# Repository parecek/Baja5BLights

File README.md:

# Baja5BLights
Lights and IR transponder for rc car Baja 5B. Front, rear lights including brake. Schematic, pcb (Kicad), Arduino sw

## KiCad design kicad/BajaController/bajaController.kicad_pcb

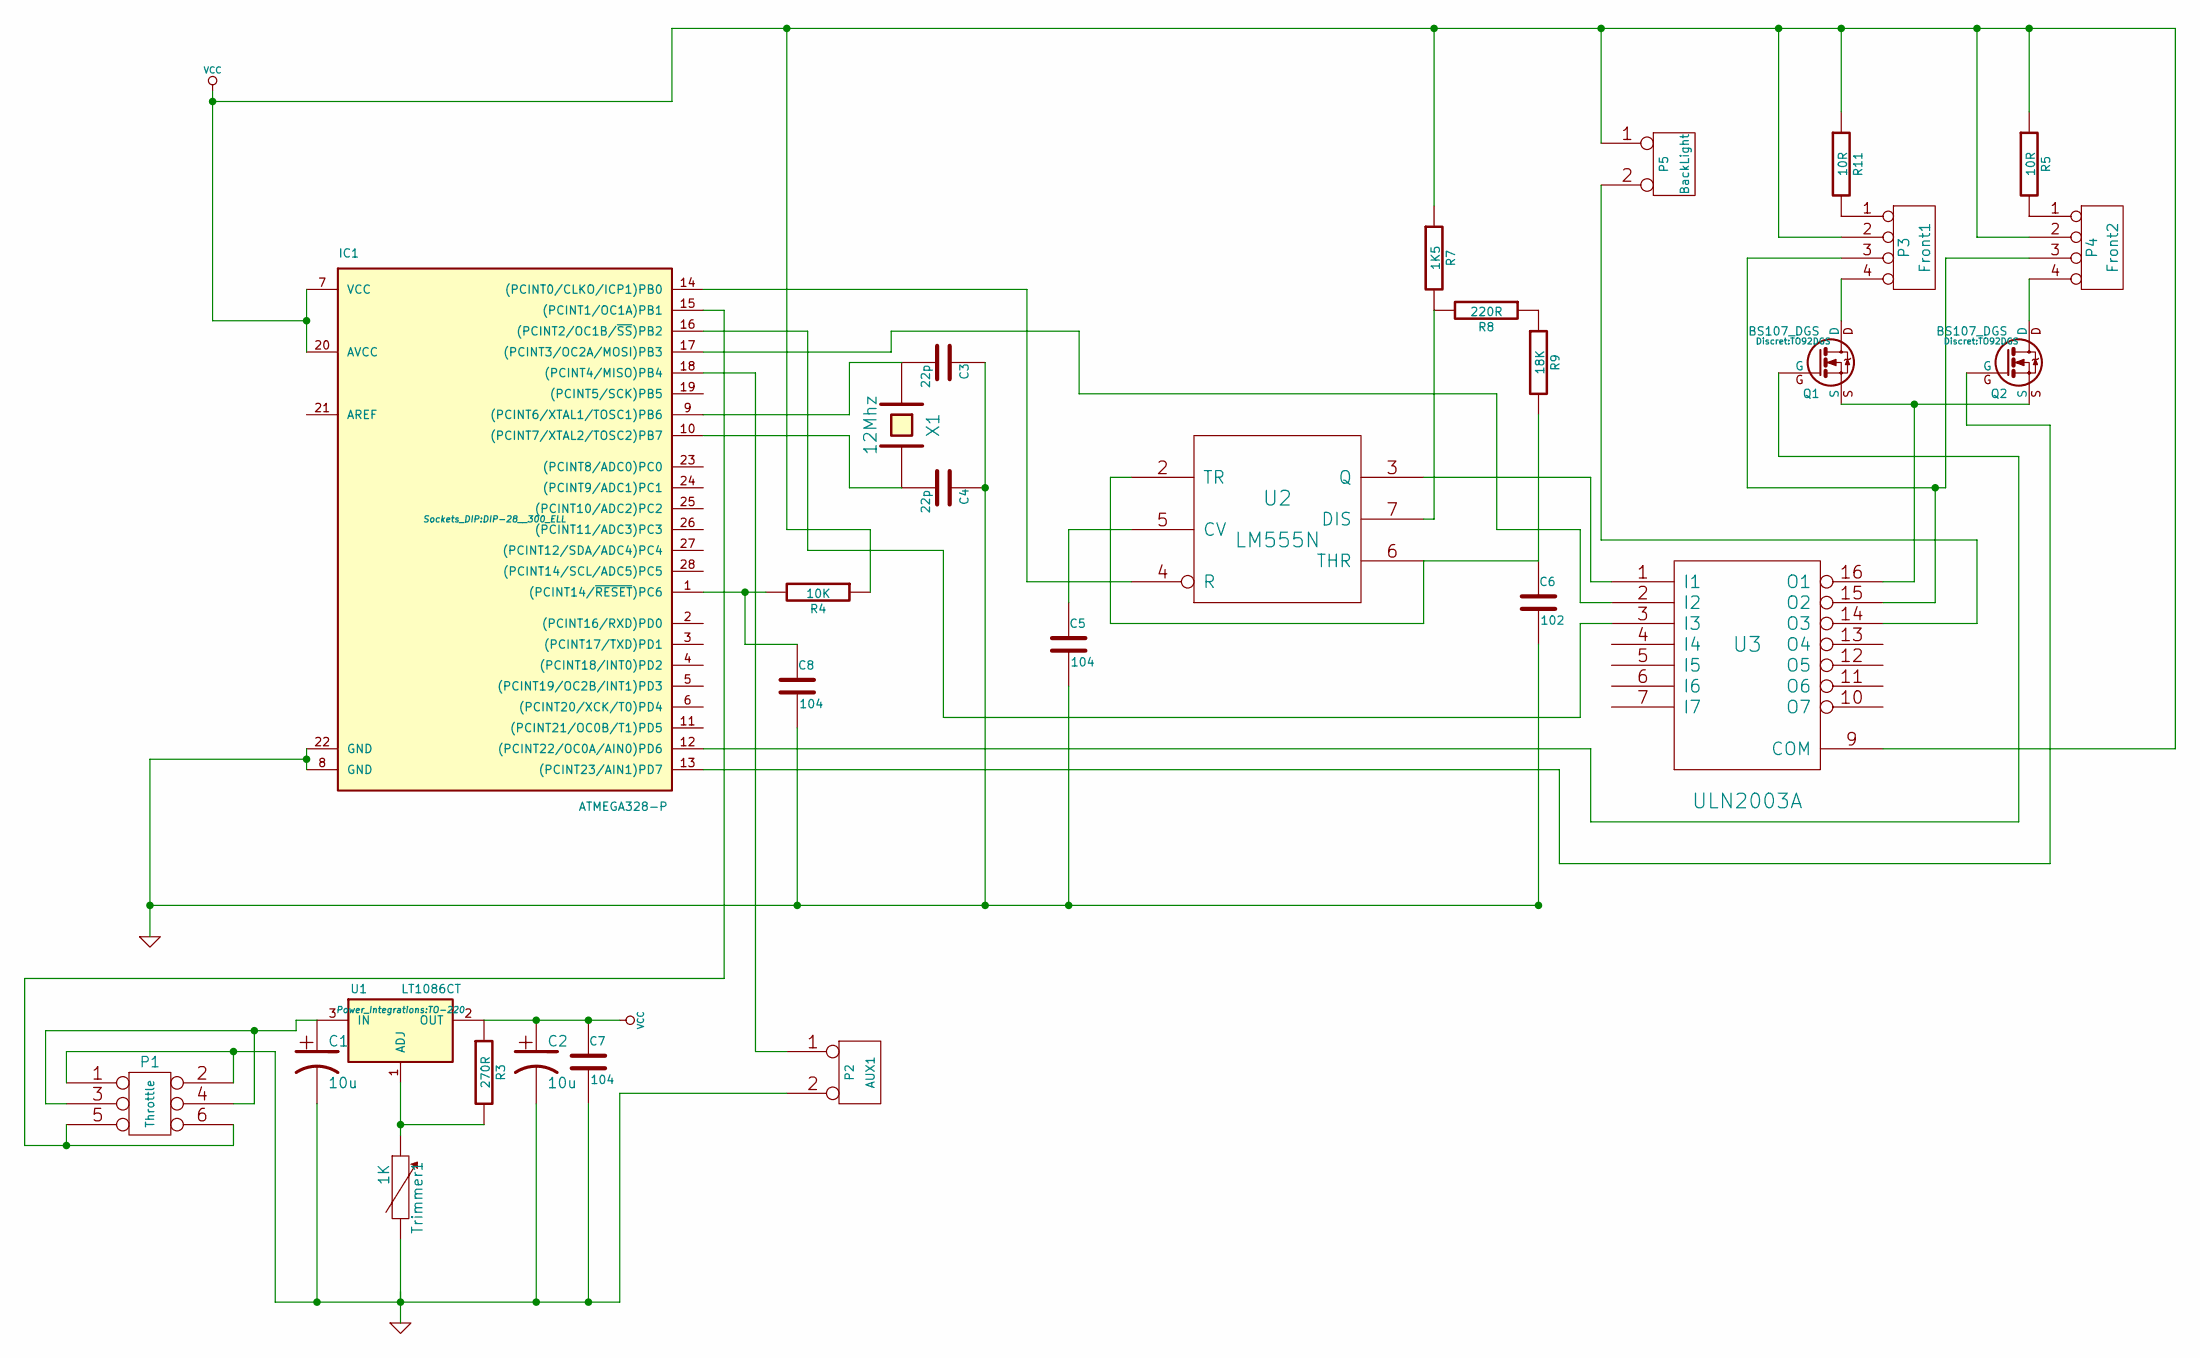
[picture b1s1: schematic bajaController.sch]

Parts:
C1, C2: 10u; C1V5
C3, C4: 22p; C_1206_HandSoldering
C5, C7, C8: 104; C2
C6: 102; C2
IC1: ATMEGA328-P; DIP-28__300_ELL
P1: Throttle; Pin_Header_Straight_2x03
P2: AUX1; Pin_Header_Straight_1x02
P3: Front1; Pin_Header_Straight_1x04
P4: Front2; Pin_Header_Straight_1x04
P5: BackLight; Pin_Header_Straight_1x02
Q1, Q2: BS107_DGS; TO92DGS
R3: 270R; R_1206_HandSoldering
R4: 10K; R_1206_HandSoldering
R5, R11: 10R; R_1206_HandSoldering
R7: 1K5; R_1206_HandSoldering
R8: 220R; R_1206_HandSoldering
R9: 18K; R_1206_HandSoldering
Trimmer1: 1K; Trimmer_CA6V5
U1: LT1086CT; TO-220
U2: LM555N; DIP-8__300_ELL
U3: ULN2003A; DIP-16__300_ELL
X1: 12Mhz; Crystal_HC49-U_Vertical

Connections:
GND: C1.2, C2.2, C3.1, C4.1, C5.2, C6.2, C7.2, C8.2, IC1.8 (GND), IC1.22 (GND), P1.1, P1.2, P2.2 (PM), Trimmer1.2, U2.1 (GND), U3.8 (GND)
unnamed: C1.1, P1.3, P1.4, U1.3 (IN)
unnamed: C3.2, IC1.9 ((PCINT6/XTAL1/TOSC1)PB6), X1.1
unnamed: C4.2, IC1.10 ((PCINT7/XTAL2/TOSC2)PB7), X1.2
unnamed: C5.1, U2.5 (CV)
unnamed: C6.1, R9.2, U2.2 (TR), U2.6 (THR)
unnamed: C8.1, IC1.1 ((PCINT14/~RESET~)PC6), R4.2
unnamed: IC1.12 ((PCINT22/OC0A/AIN0)PD6), Q1.G
unnamed: IC1.13 ((PCINT23/AIN1)PD7), Q2.G
unnamed: IC1.14 ((PCINT0/CLKO/ICP1)PB0), U2.4 (R)
unnamed: IC1.15 ((PCINT1/OC1A)PB1), P1.5, P1.6
unnamed: IC1.16 ((PCINT2/OC1B/~SS~)PB2), U3.3 (I3)
unnamed: IC1.17 ((PCINT3/OC2A/MOSI)PB3), U3.2 (I2)
unnamed: IC1.18 ((PCINT4/MISO)PB4), P2.1
unnamed: P3.1, R11.2
unnamed: P3.3, P4.3, U3.15 (O2)
unnamed: P3.4, Q1.D
unnamed: P4.1, R5.2
unnamed: P4.4, Q2.D
unnamed: P5.2 (PM), U3.14 (O3)
unnamed: Q1.S, Q2.S, U3.16 (O1)
unnamed: R3.2, Trimmer1.1, U1.1 (ADJ)
unnamed: R7.2, R8.2, U2.7 (DIS)
unnamed: R8.1, R9.1
unnamed: U2.3 (Q), U3.1 (I1)
VCC: C2.1, C7.1, IC1.7 (VCC), IC1.20 (AVCC), P3.2, P4.2, P5.1, R3.1, R4.1, R5.1, R7.1, R11.1, U1.2 (OUT), U2.8 (VCC), U3.9 (COM)

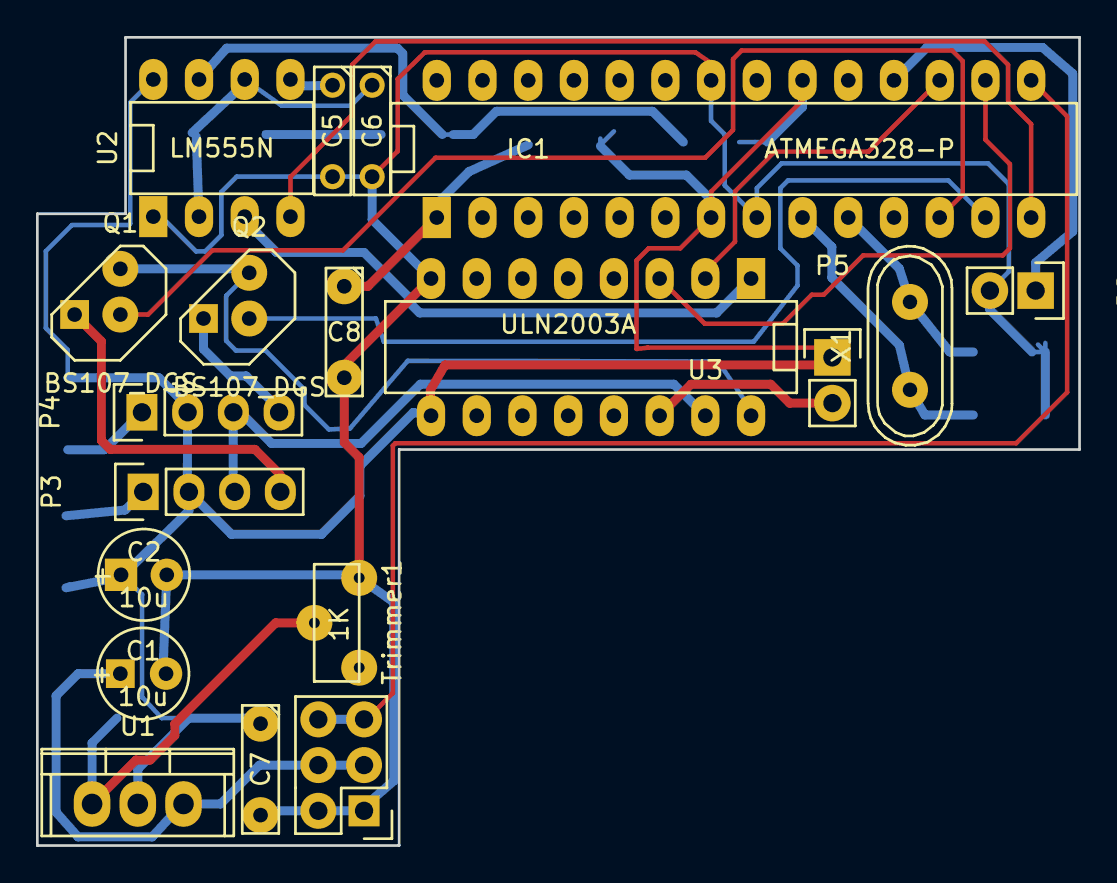
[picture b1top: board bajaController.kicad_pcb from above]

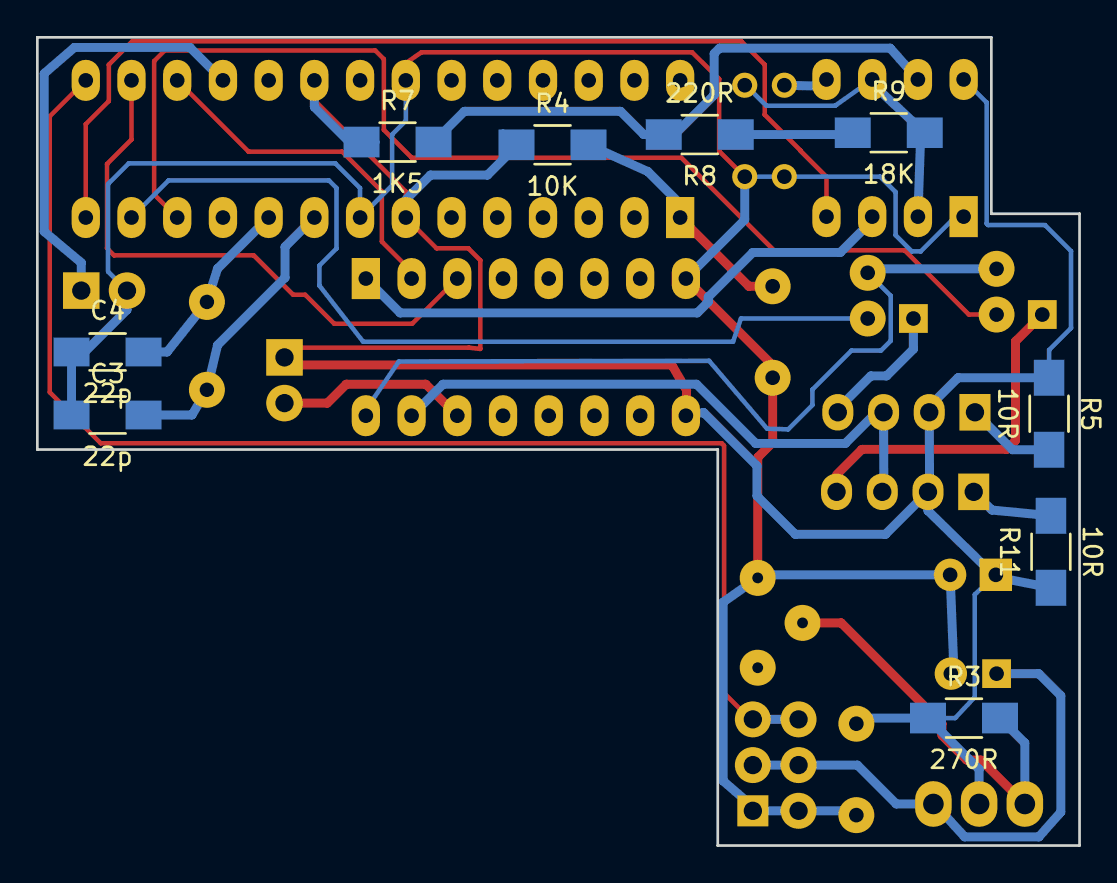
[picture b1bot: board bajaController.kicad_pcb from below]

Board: 2 copper layers, 57.9 x 44.9 mm, 28 parts (9 on the bottom side), 26 nets.

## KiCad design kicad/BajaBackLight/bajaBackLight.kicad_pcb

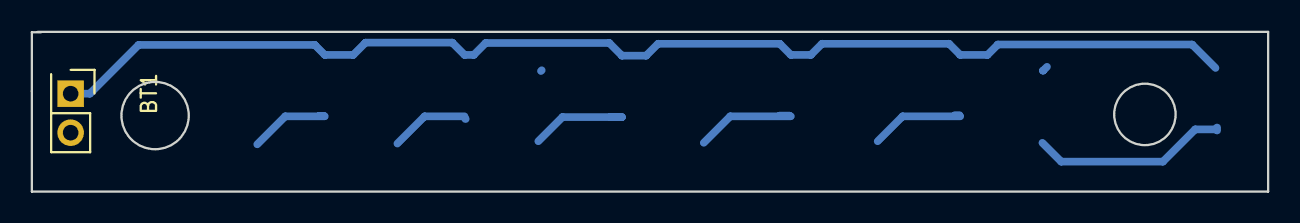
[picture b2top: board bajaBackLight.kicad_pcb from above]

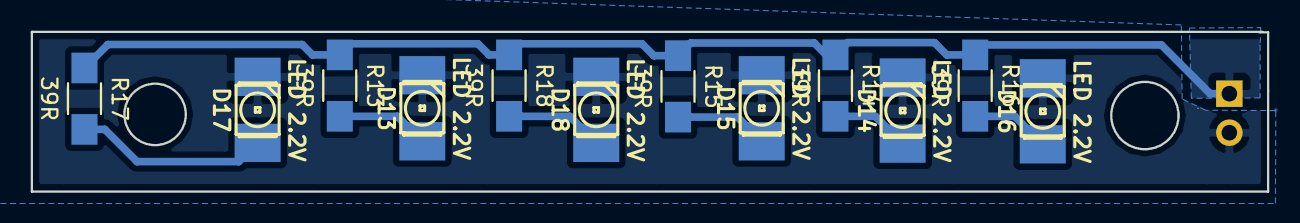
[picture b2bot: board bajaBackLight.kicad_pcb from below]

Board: 2 copper layers, 80.5 x 10.4 mm, 13 parts (12 on the bottom side), 8 nets.

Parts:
BT1: BATTERY; Pin_Header_Straight_2x01
D13, D14, D15, D16, D17, D18: LED 2.2V; LED-3528
R13, R14, R15, R16, R17, R18: 39R; R_1206_HandSoldering

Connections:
GND: BT1.2, D13.2, D14.2, D15.2, D16.2, D17.2, D18.2
unnamed: D13.1, R13.2
unnamed: D14.1, R14.2
unnamed: D15.1, R15.2
unnamed: D16.1, R16.2
unnamed: D17.1, R17.2
unnamed: D18.1, R18.2
VCC: BT1.1, R13.1, R14.1, R15.1, R16.1, R17.1, R18.1

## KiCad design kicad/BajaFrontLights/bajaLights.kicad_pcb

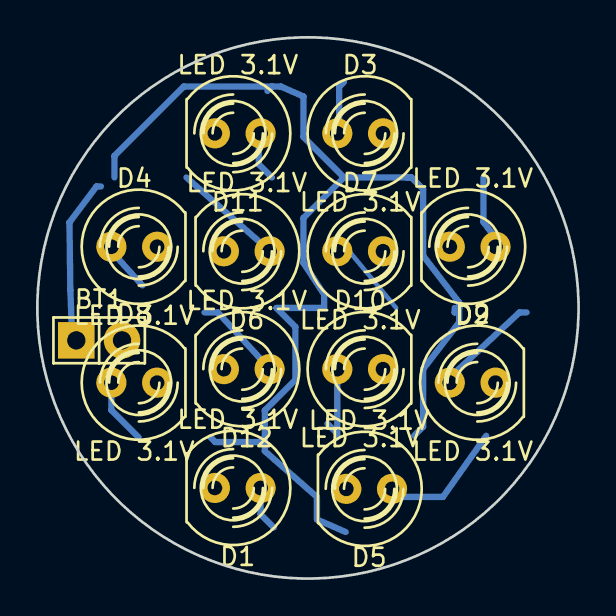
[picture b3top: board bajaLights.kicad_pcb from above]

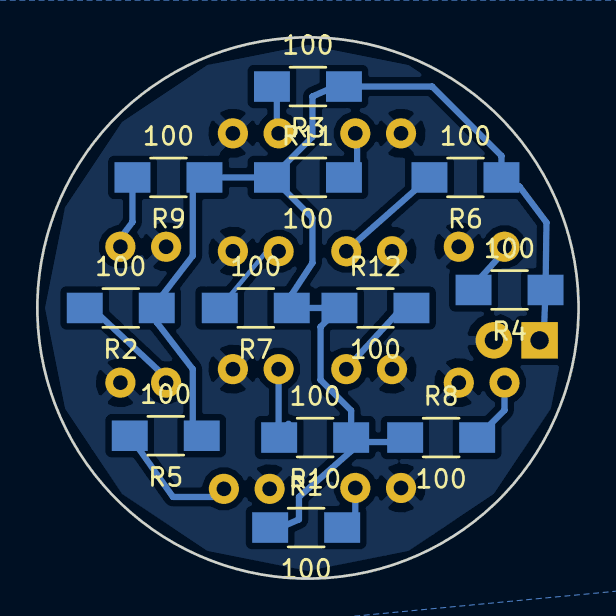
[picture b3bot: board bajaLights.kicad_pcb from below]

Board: 2 copper layers, 30.1 x 30.1 mm, 25 parts (12 on the bottom side), 14 nets.

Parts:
BT1: 3.3V; Pin_Header_Straight_1x02
D1, D2, D3, D4, D5, D6, D7, D8, D9, D10, D11, D12: LED 3.1V; LED-5MM
R1, R2, R3, R4, R5, R6, R7, R8, R9, R10, R11, R12: 100; R_1206_HandSoldering

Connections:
GND: BT1.2, D1.2, D2.2, D3.2, D4.2, D5.2, D6.2, D7.2, D8.2, D9.2, D10.2, D11.2, D12.2
unnamed: D1.1, R1.2
unnamed: D2.1, R2.2
unnamed: D3.1, R3.2
unnamed: D4.1, R4.2
unnamed: D5.1, R5.2
unnamed: D6.1, R6.2
unnamed: D7.1, R7.2
unnamed: D8.1, R8.2
unnamed: D9.1, R9.2
unnamed: D10.1, R10.2
unnamed: D11.1, R11.2
unnamed: D12.1, R12.2
VCC: BT1.1, R1.1, R2.1, R3.1, R4.1, R5.1, R6.1, R7.1, R8.1, R9.1, R10.1, R11.1, R12.1

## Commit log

2015-03-25 Adding images
